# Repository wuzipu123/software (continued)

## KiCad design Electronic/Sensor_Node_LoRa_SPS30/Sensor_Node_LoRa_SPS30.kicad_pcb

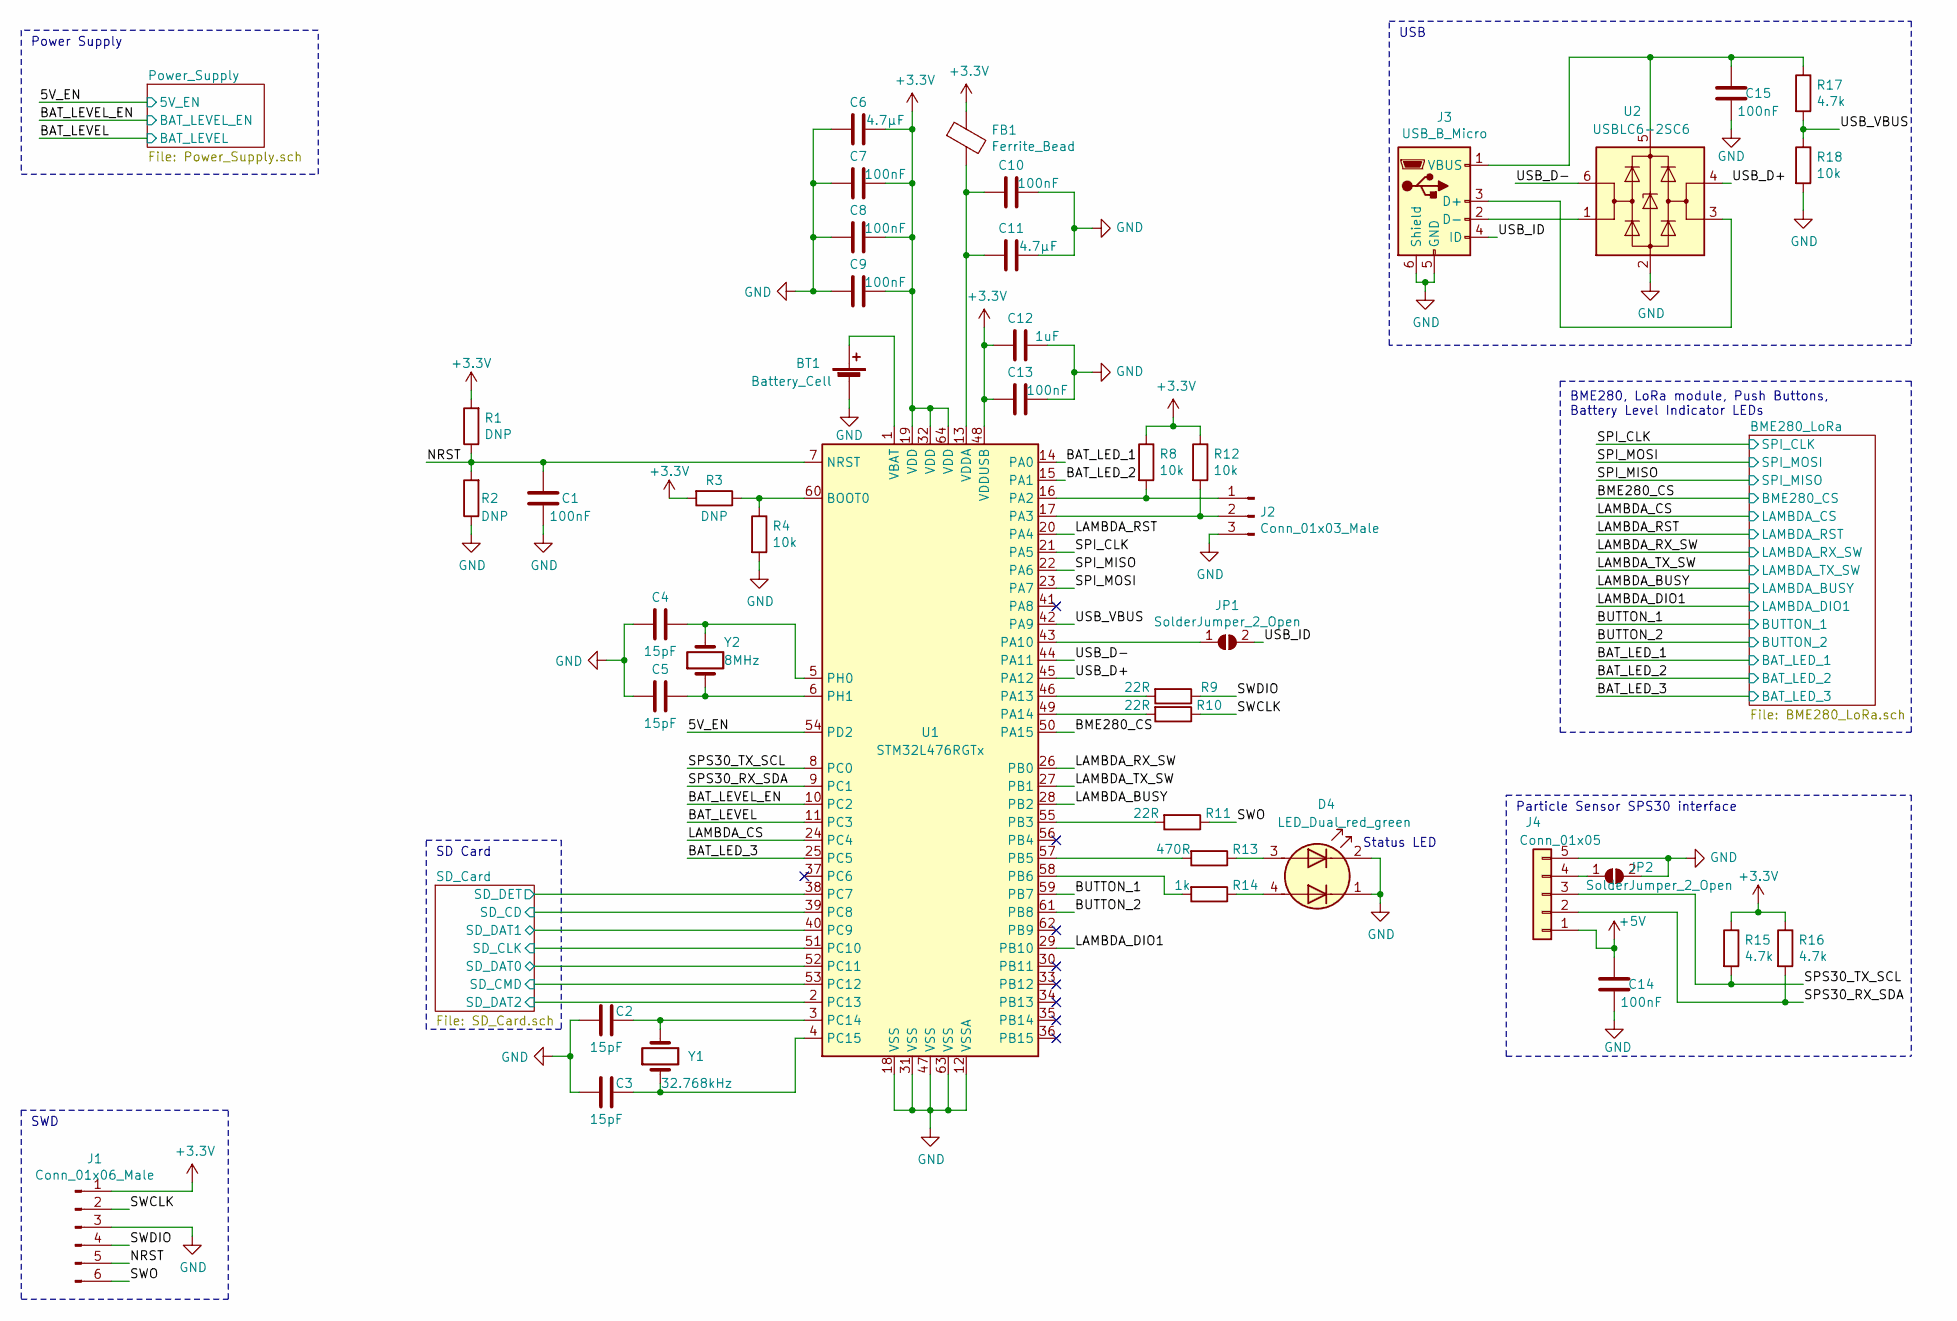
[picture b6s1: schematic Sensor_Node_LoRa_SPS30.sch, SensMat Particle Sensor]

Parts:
BT1: Battery_Cell; BatteryHolder_Keystone_2998_1x6.8mm
C1, C7, C8, C9, C13, C14, C15: 100nF; C_0603_1608Metric_Pad1.05x0.95mm_HandSolder
C2, C3, C4, C5: 15pF; C_0603_1608Metric_Pad1.05x0.95mm_HandSolder
C6, C11: 4.7µF; C_0603_1608Metric_Pad1.05x0.95mm_HandSolder
C10: 100nF; C_0603_1608Metric_Pad1.05x0.95mm_HandSolder; Digi-Key_PN test
C12: 1uF; C_0603_1608Metric_Pad1.05x0.95mm_HandSolder
D4: LED_Dual_red_green; LED_WUERTH_WL-SBCD_0805
FB1: Ferrite_Bead; L_0805_2012Metric_Pad1.15x1.40mm_HandSolder
J1: Conn_01x06_Male; PinHeader_1x06_P2.54mm_Vertical
J2: Conn_01x03_Male; PinHeader_1x03_P2.54mm_Vertical
J3: USB_B_Micro; USB_Micro-B_GCT_USB3076-30-A
J4: Conn_01x05; JST_ZH_B5B-ZH-R_1x05_P1.50mm_Vertical
JP1, JP2: SolderJumper_2_Open; SolderJumper-2_P1.3mm_Open_TrianglePad1.0x1.5mm
R1, R2, R3: DNP; R_0603_1608Metric_Pad1.05x0.95mm_HandSolder
R4, R8, R12, R18: 10k; R_0603_1608Metric_Pad1.05x0.95mm_HandSolder
R9, R10, R11: 22R; R_0603_1608Metric_Pad1.05x0.95mm_HandSolder
R13: 470R; R_0603_1608Metric_Pad1.05x0.95mm_HandSolder
R14: 1k; R_0603_1608Metric_Pad1.05x0.95mm_HandSolder
R15, R16, R17: 4.7k; R_0603_1608Metric_Pad1.05x0.95mm_HandSolder
U1: STM32L476RGTx; LQFP-64_10x10mm_P0.5mm
U2: USBLC6-2SC6; SOT-23-6_Handsoldering
Y1: 32.768kHz; Crystal_SMD_3215-2Pin_3.2x1.5mm_HandSoldering
Y2: 8MHz; Crystal_SMD_5032-2Pin_5.0x3.2mm_HandSoldering

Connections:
+3V3: C6.1, C7.1, C8.1, C9.1, C12.2, C13.2, FB1.1, J1.1, R1.2, R3.2, R8.1, R12.1, R15.1, R16.1, U1.19 (VDD), U1.32 (VDD), U1.48 (VDDUSB), U1.64 (VDD); also elsewhere on the board
+5V: C14.2, J4.1; also elsewhere on the board
/5V_EN: U1.54 (PD2); also elsewhere on the board
/BAT_LED_1: U1.14 (PA0); also elsewhere on the board
/BAT_LED_2: U1.15 (PA1); also elsewhere on the board
/BAT_LED_3: U1.25 (PC5); also elsewhere on the board
/BAT_LEVEL: U1.11 (PC3); also elsewhere on the board
/BAT_LEVEL_EN: U1.10 (PC2); also elsewhere on the board
/BME280_CS: U1.50 (PA15); also elsewhere on the board
/BUTTON_1: U1.59 (PB7); also elsewhere on the board
/BUTTON_2: U1.61 (PB8); also elsewhere on the board
/LAMBDA_BUSY: U1.28 (PB2); also elsewhere on the board
/LAMBDA_CS: U1.24 (PC4); also elsewhere on the board
/LAMBDA_DIO1: U1.29 (PB10); also elsewhere on the board
/LAMBDA_RST: U1.20 (PA4); also elsewhere on the board
/LAMBDA_RX_SW: U1.26 (PB0); also elsewhere on the board
/LAMBDA_TX_SW: U1.27 (PB1); also elsewhere on the board
/NRST: C1.2, J1.5, R1.1, R2.2, U1.7 (NRST)
/SD_Card/SD_CD: U1.39 (PC8); also elsewhere on the board
/SD_Card/SD_CLK: U1.51 (PC10); also elsewhere on the board
/SD_Card/SD_CMD: U1.53 (PC12); also elsewhere on the board
/SD_Card/SD_DAT0: U1.52 (PC11); also elsewhere on the board
/SD_Card/SD_DAT1: U1.40 (PC9); also elsewhere on the board
/SD_Card/SD_DAT2: U1.2 (PC13); also elsewhere on the board
/SD_Card/SD_DET: U1.38 (PC7); also elsewhere on the board
/SPI_CLK: U1.21 (PA5); also elsewhere on the board
/SPI_MISO: U1.22 (PA6); also elsewhere on the board
/SPI_MOSI: U1.23 (PA7); also elsewhere on the board
/SPS30_RX_SDA: J4.2, R16.2, U1.9 (PC1)
/SPS30_TX_SCL: J4.3, R15.2, U1.8 (PC0)
/SWCLK: J1.2, R10.1
/SWDIO: J1.4, R9.1
/SWO: J1.6, R11.1
/USB_D+: U1.45 (PA12), U2.4 (I/O2)
/USB_D-: U1.44 (PA11), U2.6 (I/O1)
/USB_ID: J3.4 (ID), JP1.2 (B)
/USB_VBUS: R17.2, R18.1, U1.42 (PA9)
GND: BT1.2 (-), C1.1, C2.1, C3.1, C4.1, C5.1, C6.2, C7.2, C8.2, C9.2, C10.1, C11.1, C12.1, C13.1, C14.1, C15.1, D4.1 (K2), D4.2 (K1), J1.3, J2.3, J3.5 (GND), J3.6 (Shield), J4.5, JP2.2 (B), R2.1, R4.2, R18.2, U1.12 (VSSA), U1.18 (VSS), U1.31 (VSS), U1.47 (VSS), U1.63 (VSS), U2.2 (GND); also elsewhere on the board
unnamed: BT1.1 (+), U1.1 (VBAT)
unnamed: C2.2, U1.3 (PC14), Y1.2
unnamed: C3.2, U1.4 (PC15), Y1.1
unnamed: C4.2, U1.5 (PH0), Y2.2
unnamed: C5.2, U1.6 (PH1), Y2.1
unnamed: C10.2, C11.2, FB1.2, U1.13 (VDDA)
unnamed: C15.2, J3.1 (VBUS), R17.1, U2.5 (VBUS)
unnamed: D4.3 (A1), R13.1
unnamed: D4.4 (A2), R14.1
unnamed: J2.1, R8.2, U1.16 (PA2)
unnamed: J2.2, R12.2, U1.17 (PA3)
unnamed: J3.2 (D-), U2.1 (I/O1)
unnamed: J3.3 (D+), U2.3 (I/O2)
unnamed: J4.4, JP2.1 (A)
unnamed: JP1.1 (A), U1.43 (PA10)
unnamed: R3.1, R4.1, U1.60 (BOOT0)
unnamed: R9.2, U1.46 (PA13)
unnamed: R10.2, U1.49 (PA14)
unnamed: R11.2, U1.55 (PB3)
unnamed: R13.2, U1.57 (PB5)
unnamed: R14.2, U1.58 (PB6)

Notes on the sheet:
SWD
BME280, LoRa module, Push Buttons, Battery Level Indicator LEDs
SD Card
Particle Sensor SPS30 interface
USB
Power Supply
Status LED

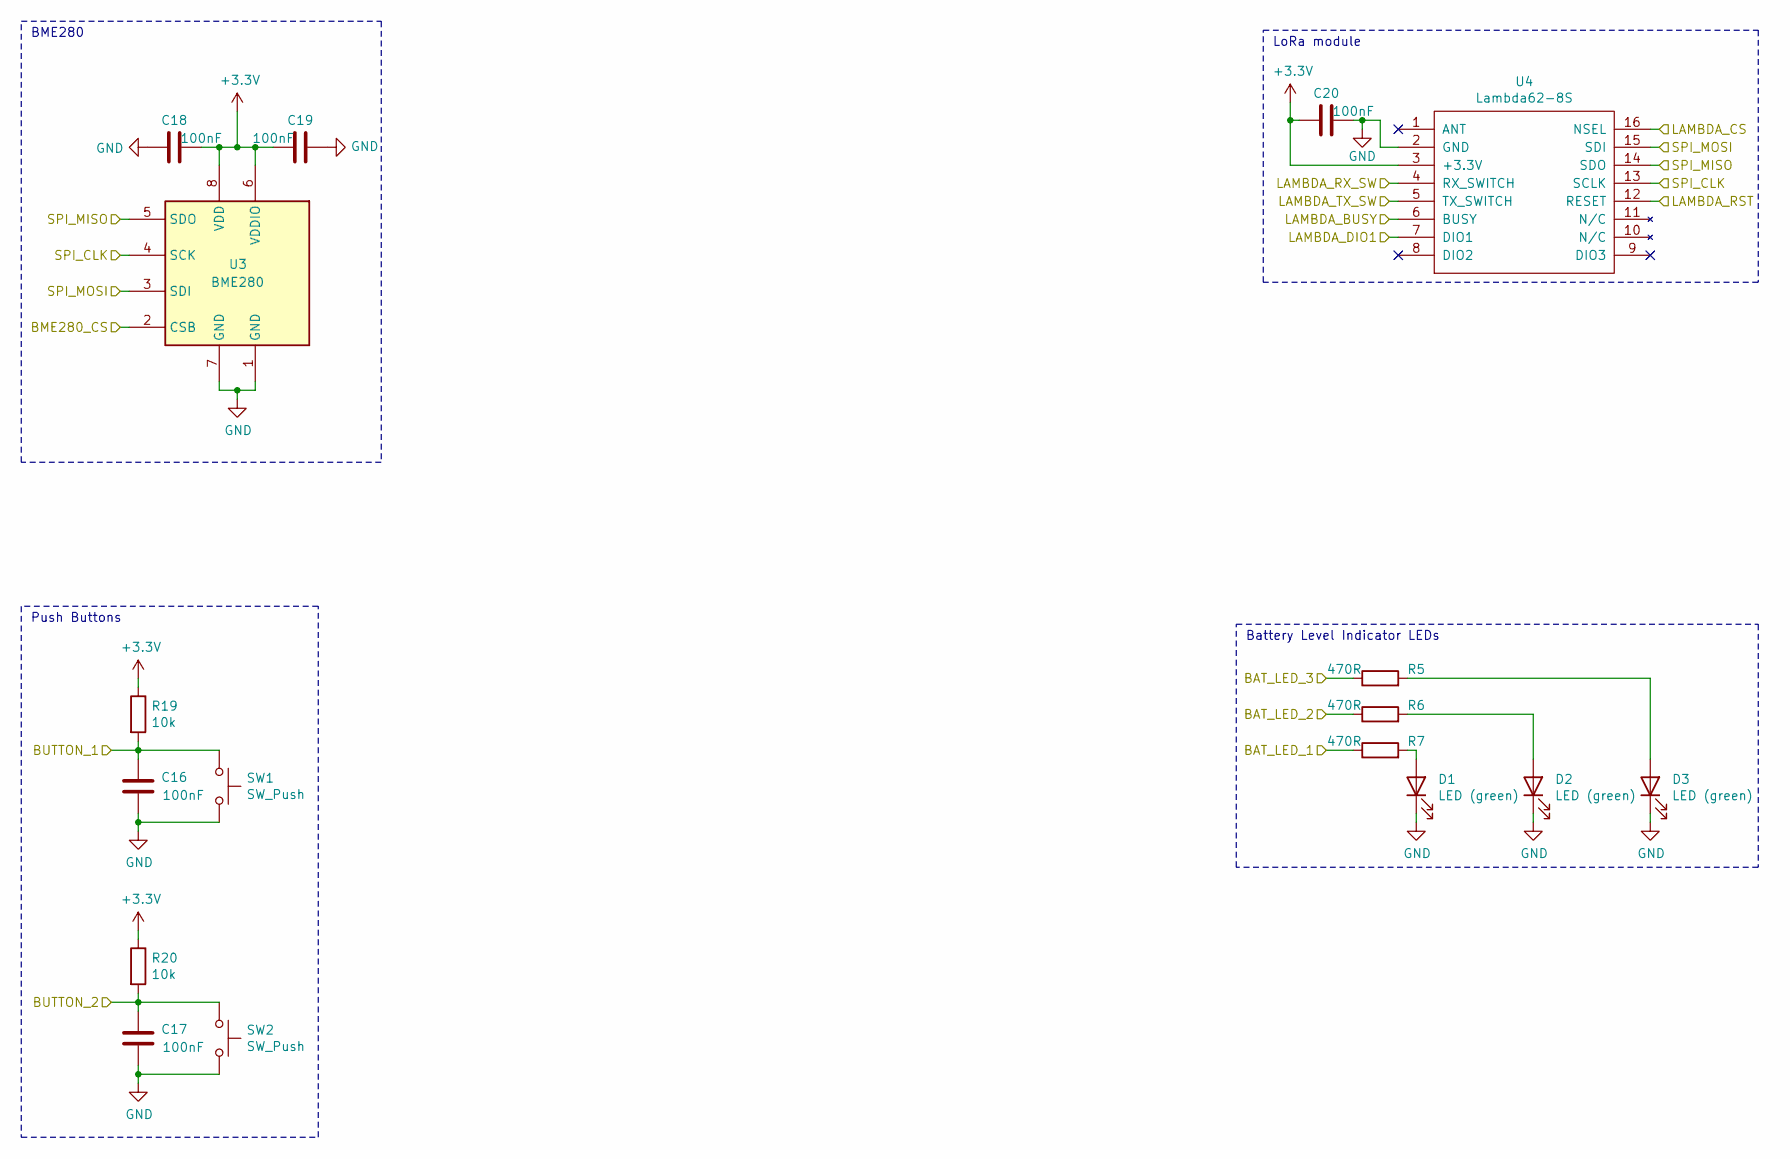
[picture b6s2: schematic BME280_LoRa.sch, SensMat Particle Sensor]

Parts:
C16, C17, C18, C19, C20: 100nF; C_0603_1608Metric_Pad1.05x0.95mm_HandSolder
D1, D2, D3: LED (green); LED_0603_1608Metric_Pad1.05x0.95mm_HandSolder
R5, R6, R7: 470R; R_0603_1608Metric_Pad1.05x0.95mm_HandSolder
R19, R20: 10k; R_0603_1608Metric_Pad1.05x0.95mm_HandSolder
SW1, SW2: SW_Push; SW_Tactile_SPST_Angled_PTS645Vx58-2LFS
U3: BME280; Bosch_LGA-8_2.5x2.5mm_P0.65mm_ClockwisePinNumbering
U4: Lambda62-8S

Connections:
+3V3: C18.1, C19.2, C20.2, R19.1, R20.1, U3.6 (VDDIO), U3.8 (VDD), U4.3 (+3.3V); also elsewhere on the board
/BAT_LED_1: R7.1; also elsewhere on the board
/BAT_LED_2: R6.1; also elsewhere on the board
/BAT_LED_3: R5.1; also elsewhere on the board
/BME280_CS: U3.2 (CSB); also elsewhere on the board
/BUTTON_1: C16.2, R19.2, SW1.1; also elsewhere on the board
/BUTTON_2: C17.2, R20.2, SW2.1; also elsewhere on the board
/LAMBDA_BUSY: U4.6 (BUSY); also elsewhere on the board
/LAMBDA_CS: U4.16 (NSEL); also elsewhere on the board
/LAMBDA_DIO1: U4.7 (DIO1); also elsewhere on the board
/LAMBDA_RST: U4.12 (RESET); also elsewhere on the board
/LAMBDA_RX_SW: U4.4 (RX_SWITCH); also elsewhere on the board
/LAMBDA_TX_SW: U4.5 (TX_SWITCH); also elsewhere on the board
/SPI_CLK: U3.4 (SCK), U4.13 (SCLK); also elsewhere on the board
/SPI_MISO: U3.5 (SDO), U4.14 (SDO); also elsewhere on the board
/SPI_MOSI: U3.3 (SDI), U4.15 (SDI); also elsewhere on the board
GND: C16.1, C17.1, C18.2, C19.1, C20.1, D1.1 (K), D2.1 (K), D3.1 (K), SW1.2, SW2.2, U3.1 (GND), U3.7 (GND), U4.2 (GND); also elsewhere on the board
unnamed: D1.2 (A), R7.2
unnamed: D2.2 (A), R6.2
unnamed: D3.2 (A), R5.2

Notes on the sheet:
LoRa module
BME280
Push Buttons
Battery Level Indicator LEDs

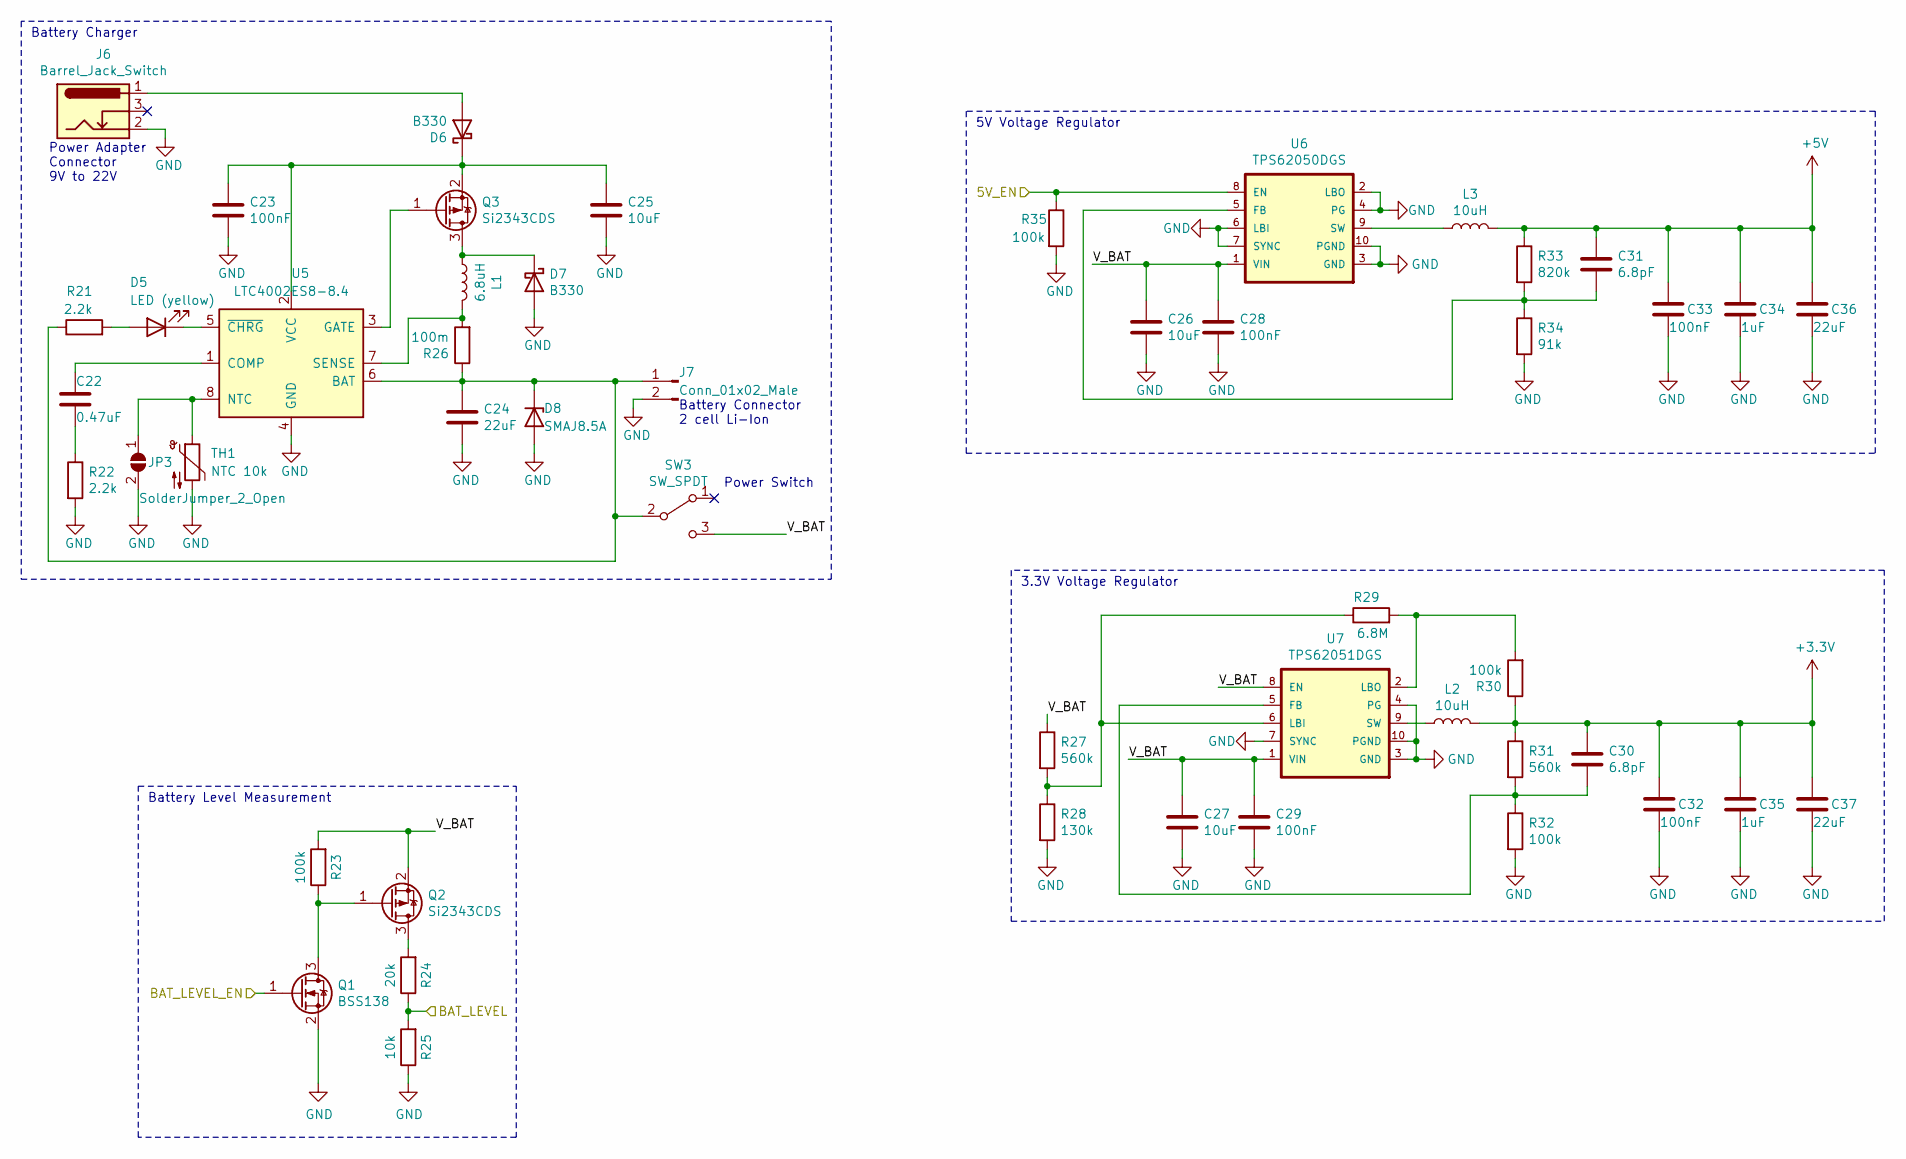
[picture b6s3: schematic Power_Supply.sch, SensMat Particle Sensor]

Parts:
C22: 0.47uF; C_0603_1608Metric_Pad1.05x0.95mm_HandSolder
C23, C28, C29, C32, C33: 100nF; C_0603_1608Metric_Pad1.05x0.95mm_HandSolder
C24, C36, C37: 22uF; C_0603_1608Metric_Pad1.05x0.95mm_HandSolder
C25, C26, C27: 10uF; C_0603_1608Metric_Pad1.05x0.95mm_HandSolder
C30, C31: 6.8pF; C_0603_1608Metric_Pad1.05x0.95mm_HandSolder
C34, C35: 1uF; C_0603_1608Metric_Pad1.05x0.95mm_HandSolder
D5: LED (yellow); LED_0603_1608Metric_Pad1.05x0.95mm_HandSolder
D6, D7: B330; D_SMB-SMC_Universal_Handsoldering
D8: SMAJ8.5A; D_SMA
J6: Barrel_Jack_Switch; BarrelJack_CUI_PJ-051A_Horizontal
J7: Conn_01x02_Male; PinSocket_1x02_P2.54mm_Vertical
JP3: SolderJumper_2_Open; SolderJumper-2_P1.3mm_Open_TrianglePad1.0x1.5mm
L1: 6.8uH; L_Wuerth_LQS-6045
L2, L3: 10uH; L_Wuerth_LQS-5040
Q1: BSS138; SOT-23
Q2, Q3: Si2343CDS; SOT-23
R21, R22: 2.2k; R_0603_1608Metric_Pad1.05x0.95mm_HandSolder
R23, R30, R32, R35: 100k; R_0603_1608Metric_Pad1.05x0.95mm_HandSolder
R24: 20k; R_0603_1608Metric_Pad1.05x0.95mm_HandSolder
R25: 10k; R_0603_1608Metric_Pad1.05x0.95mm_HandSolder
R26: 100m; R_1206_3216Metric_Pad1.42x1.75mm_HandSolder
R27, R31: 560k; R_0603_1608Metric_Pad1.05x0.95mm_HandSolder
R28: 130k; R_0603_1608Metric_Pad1.05x0.95mm_HandSolder
R29: 6.8M; R_0603_1608Metric_Pad1.05x0.95mm_HandSolder
R33: 820k; R_0603_1608Metric_Pad1.05x0.95mm_HandSolder
R34: 91k; R_0603_1608Metric_Pad1.05x0.95mm_HandSolder
SW3: SW_SPDT; SW_CK_SK-12F17-G_7_SPDT_Angled
TH1: NTC 10k; R_1206_3216Metric_Pad1.42x1.75mm_HandSolder
U5: LTC4002ES8-8.4; SOIC-8_3.9x4.9mm_P1.27mm
U6: TPS62050DGS; MSOP-10_3x3mm_P0.5mm
U7: TPS62051DGS; MSOP-10_3x3mm_P0.5mm

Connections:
+3V3: C30.1, C32.1, C35.1, C37.1, L2.2, R30.1, R31.1; also elsewhere on the board
+5V: C31.1, C33.1, C34.1, C36.1, L3.2, R33.1; also elsewhere on the board
/5V_EN: R35.1, U6.8 (EN); also elsewhere on the board
/BAT_LEVEL: R24.1, R25.2; also elsewhere on the board
/BAT_LEVEL_EN: Q1.1 (G); also elsewhere on the board
/Power_Supply/V_BAT: C26.1, C27.1, C28.1, C29.1, Q2.2 (S), R23.2, R27.1, SW3.3 (C), U6.1 (VIN), U7.1 (VIN), U7.8 (EN)
GND: C23.2, C24.2, C25.2, C26.2, C27.2, C28.2, C29.2, C32.2, C33.2, C34.2, C35.2, C36.2, C37.2, D7.2 (A), D8.2 (A2), J6.2, J7.2, JP3.2 (B), Q1.2 (S), R22.2, R25.1, R28.2, R32.2, R34.2, R35.2, TH1.2, U5.4 (GND), U6.2 (LBO), U6.3 (GND), U6.4 (PG), U6.6 (LBI), U6.7 (SYNC), U6.10 (PGND), U7.3 (GND), U7.4 (PG), U7.7 (SYNC), U7.10 (PGND); also elsewhere on the board
unnamed: C22.1, U5.1 (COMP)
unnamed: C22.2, R22.1
unnamed: C23.1, C25.1, D6.1 (K), Q3.2 (S), U5.2 (VCC)
unnamed: C24.1, D8.1 (A1), J7.1, R21.1, R26.1, SW3.2 (B), U5.6 (BAT)
unnamed: C30.2, R31.2, R32.1, U7.5 (FB)
unnamed: C31.2, R33.2, R34.1, U6.5 (FB)
unnamed: D5.1 (K), U5.5 (~CHRG~)
unnamed: D5.2 (A), R21.2
unnamed: D6.2 (A), J6.1
unnamed: D7.1 (K), L1.1, Q3.3 (D)
unnamed: JP3.1 (A), TH1.1, U5.8 (NTC)
unnamed: L1.2, R26.2, U5.7 (SENSE)
unnamed: L2.1, U7.9 (SW)
unnamed: L3.1, U6.9 (SW)
unnamed: Q1.3 (D), Q2.1 (G), R23.1
unnamed: Q2.3 (D), R24.2
unnamed: Q3.1 (G), U5.3 (GATE)
unnamed: R27.2, R28.1, R29.1, U7.6 (LBI)
unnamed: R29.2, R30.2, U7.2 (LBO)

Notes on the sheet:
Battery Connector 2 cell Li-Ion
Power Switch
Power Adapter Connector 9V to 22V
5V Voltage Regulator
3.3V Voltage Regulator
Battery Level Measurement
Battery Charger

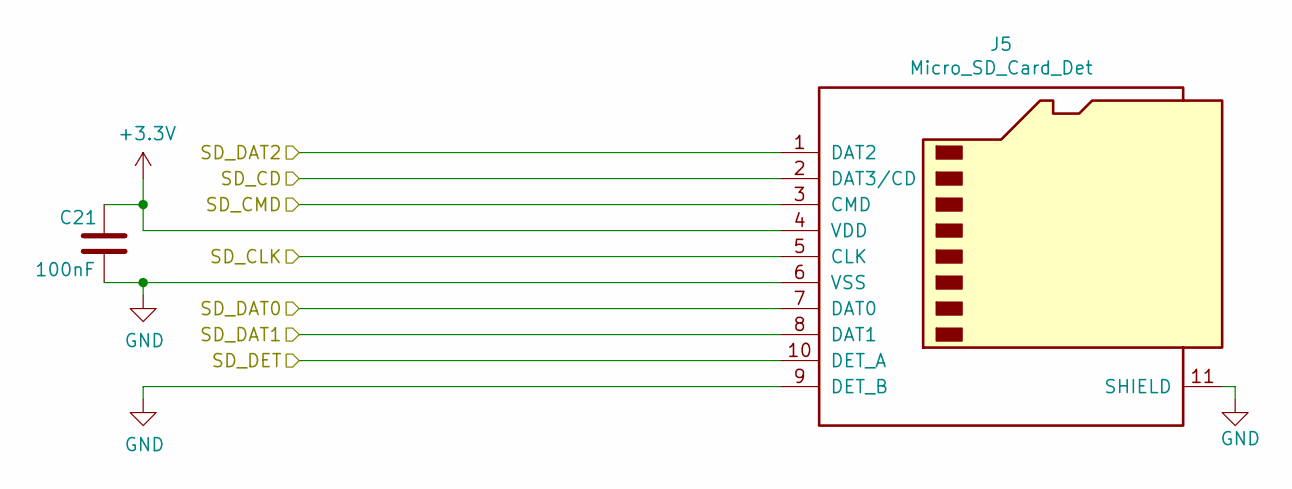
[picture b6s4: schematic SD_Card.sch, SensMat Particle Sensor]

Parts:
C21: 100nF; C_0603_1608Metric_Pad1.05x0.95mm_HandSolder
J5: Micro_SD_Card_Det; microSD_HC_Hirose_DM3AT-SF-PEJM5

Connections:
+3V3: C21.1, J5.4 (VDD); also elsewhere on the board
/SD_Card/SD_CD: J5.2 (DAT3/CD); also elsewhere on the board
/SD_Card/SD_CLK: J5.5 (CLK); also elsewhere on the board
/SD_Card/SD_CMD: J5.3 (CMD); also elsewhere on the board
/SD_Card/SD_DAT0: J5.7 (DAT0); also elsewhere on the board
/SD_Card/SD_DAT1: J5.8 (DAT1); also elsewhere on the board
/SD_Card/SD_DAT2: J5.1 (DAT2); also elsewhere on the board
/SD_Card/SD_DET: J5.10 (DET_A); also elsewhere on the board
GND: C21.2, J5.6 (VSS), J5.9 (DET_B), J5.11 (SHIELD); also elsewhere on the board

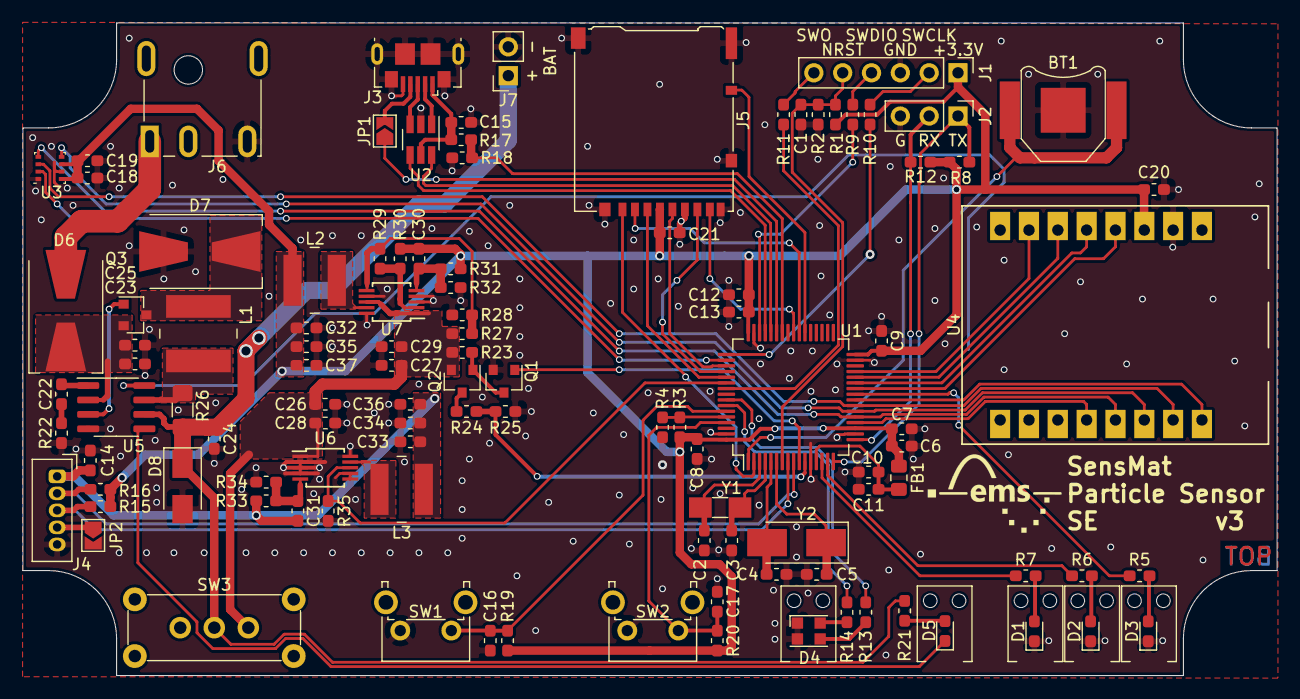
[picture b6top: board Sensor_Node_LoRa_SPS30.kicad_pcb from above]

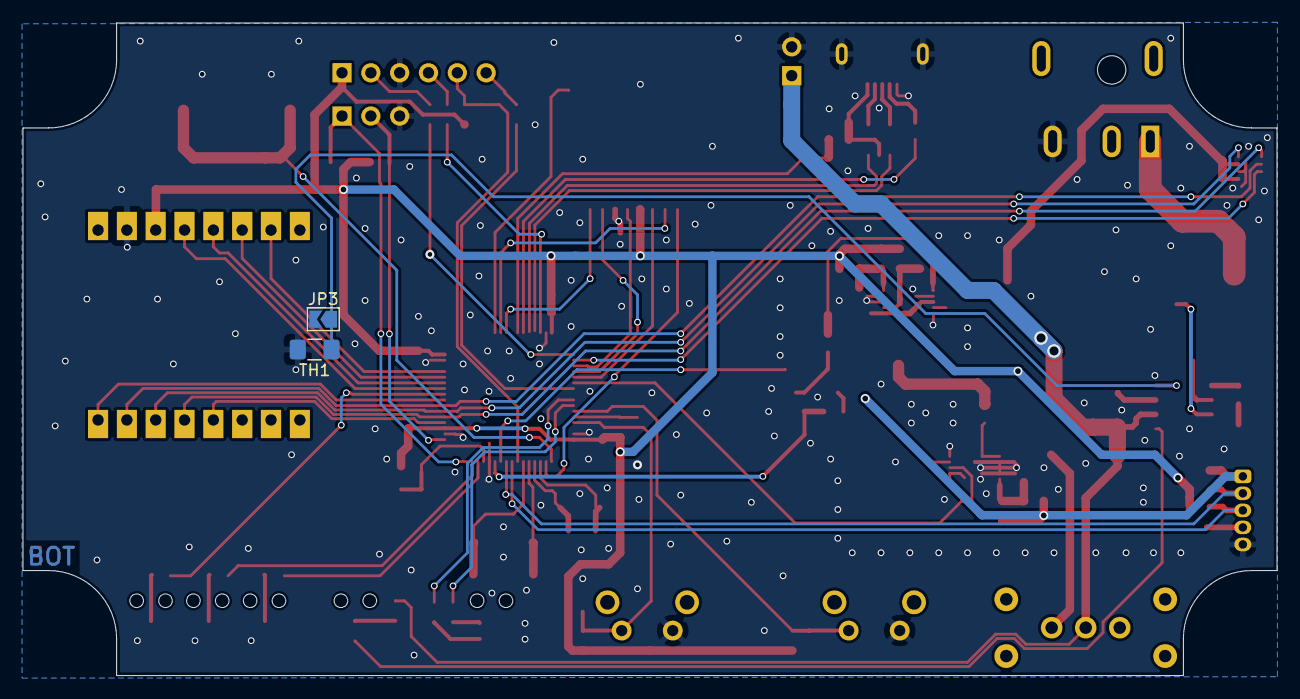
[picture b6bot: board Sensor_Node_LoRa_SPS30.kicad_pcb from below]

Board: 2 copper layers, 110.5 x 57.5 mm, 111 parts (2 on the bottom side), 82 nets.

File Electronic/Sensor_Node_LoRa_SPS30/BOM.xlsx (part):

Source: | SensMat/Electronic/Sensor_Node_LoRa_SPS30/Sensor_Node_LoRa_SPS30.sch
Date: | Do 10 May 2021 10:51:11
Tool: | Eeschema 5.1.8
Generator: | /usr/share/kicad/plugins/bom_csv_grouped_by_value_with_fp.py
Component Count: | 111
Ref | Qnty | Order | Value | Cmp name | Footprint | Description | Digikey Nr. | Digikey-Link
BT1, | 1 |  | Battery_Cell | Battery_Cell | Battery:BatteryHolder_Keystone_2998_1x6.8mm | Single-cell battery holder | 36-2998-ND | https://www.digikey.at/products/de?keywords=36-2998-ND
C1, C7, C8, C9, C10, C13, C14, C15, C16, C17, C18, C19, C20, C21, C23, C28, C29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 | 19 |  | 100nF | C | Capacitor_SMD:C_0603_1608Metric_Pad1.05x0.95mm_HandSolder | Unpolarized capacitor | 1276-1857-1-ND | https://www.digikey.at/products/de?keywords=1276-1857-1-ND
C2, C3, C4, C5, | 4 |  | 15pF | C | Capacitor_SMD:C_0603_1608Metric_Pad1.05x0.95mm_HandSolder | Unpolarized capacitor | 1276-1296-1-ND | https://www.digikey.at/products/de?keywords=1276-1296-1-ND
C6, C11, | 2 |  | 4.7µF | C | Capacitor_SMD:C_0603_1608Metric_Pad1.05x0.95mm_HandSolder | Unpolarized capacitor | 1276-1907-1-ND | https://www.digikey.at/products/de?keywords=1276-1907-1-ND
C12, C34, C35, | 3 |  | 1uF | C | Capacitor_SMD:C_0603_1608Metric_Pad1.05x0.95mm_HandSolder | Unpolarized capacitor | 1276-1182-1-ND | https://www.digikey.at/products/de?keywords=1276-1182-1-ND
C22, | 1 |  | 0.47uF | C | Capacitor_SMD:C_0603_1608Metric_Pad1.05x0.95mm_HandSolder | Unpolarized capacitor | 1276-1895-1-ND | https://www.digikey.at/products/de?keywords=1276-1895-1-ND
C24, C36, C37, | 3 |  | 22uF | C | Capacitor_SMD:C_0603_1608Metric_Pad1.05x0.95mm_HandSolder | Unpolarized capacitor | 445-9077-1-ND | https://www.digikey.at/products/de?keywords=445-9077-1-ND
C25, C26, C27, | 3 |  | 10uF | C | Capacitor_SMD:C_0603_1608Metric_Pad1.05x0.95mm_HandSolder | Unpolarized capacitor | 587-6023-1-ND | https://www.digikey.at/products/de?keywords=587-6023-1-ND
C30, C31, | 2 |  | 6.8pF | C | Capacitor_SMD:C_0603_1608Metric_Pad1.05x0.95mm_HandSolder | Unpolarized capacitor | 1276-1793-1-ND | https://www.digikey.at/products/de?keywords=1276-1793-1-ND
D1, D2, D3, | 3 |  | LED (green) | LED | LED_SMD:LED_0603_1608Metric_Pad1.05x0.95mm_HandSolder | Light emitting diode green | 732-4980-1-ND | https://www.digikey.at/products/de?keywords=732-4980-1-ND
D4, | 1 |  | LED_Dual_red_green | LED_Dual_CCAA | LED_SMD:LED_WUERTH_WL-SBCD_0805 | Dual LED, cathodes on pins 1 and 2 | 732-150080RV54050CT-ND | https://www.digikey.at/products/de?keywords=732-150080RV54050CT-ND
D5, | 1 |  | LED (yellow) | LED | LED_SMD:LED_0603_1608Metric_Pad1.05x0.95mm_HandSolder | Light emitting diode yellow | 732-4981-6-ND | https://www.digikey.at/products/de?keywords=732-4981-6-ND
D6, D7, | 2 |  | B330 | B330 | Diode_SMD:D_SMB-SMC_Universal_Handsoldering | 30V 3A Schottky Barrier Rectifier Diode, SMC | B330-FDICT-ND | https://www.digikey.at/products/de?keywords=B330-FDICT-ND
D8, | 1 |  | SMAJ8.5A | 5KPxxA | Diode_SMD:D_SMA | 5000W unidirectional Transient Voltage Suppressor, P-600 | SMAJ8.5A-FDICT-ND | https://www.digikey.at/products/de?keywords=SMAJ8.5A-FDICT-ND
FB1, | 1 |  | Ferrite_Bead | Ferrite_Bead | Inductor_SMD:L_0805_2012Metric_Pad1.15x1.40mm_HandSolder | Ferrite bead | 541-4362-1-ND | https://www.digikey.at/products/de?keywords=541-4362-1-ND
J1, | 1 |  | Conn_01x06_Male | Conn_01x06_Male | Connector_PinHeader_2.54mm:PinHeader_1x06_P2.54mm_Vertical | Generic connector, single row, 01x06, |  | https://www.digikey.at/products/de?keywords=
J2, | 1 |  | Conn_01x03_Male | Conn_01x03_Male | Connector_PinHeader_2.54mm:PinHeader_1x03_P2.54mm_Vertical | Generic connector, single row, 01x03, |  | https://www.digikey.at/products/de?keywords=
J3, | 1 |  | USB_B_Micro | USB_B_Micro | Connector_USB:USB_Micro-B_GCT_USB3076-30-A | USB Micro Type B connector | 2073-USB3076-30-ACT-ND | https://www.digikey.at/products/de?keywords=2073-USB3076-30-ACT-ND
J4, | 1 |  | Conn_01x05 | Conn_01x05 | Connector_JST:JST_ZH_B5B-ZH-R_1x05_P1.50mm_Vertical | Generic connector, single row, 01x05, | 455-1660-ND | https://www.digikey.at/products/de?keywords=455-1660-ND
J5, | 1 |  | Micro_SD_Card_Det | Micro_SD_Card_Det | Connector_Card:microSD_HC_Hirose_DM3AT-SF-PEJM5 | Micro SD Card Socket with card detection pins | HR1964CT-ND | https://www.digikey.at/products/de?keywords=HR1964CT-ND
J6, | 1 |  | Barrel_Jack_Switch | Barrel_Jack_Switch | Connector_BarrelJack:BarrelJack_CUI_PJ-051A_Horizontal | DC Barrel Jack with an internal switch | CP-051A-ND | https://www.digikey.at/products/de?keywords=CP-051A-ND
J7, | 1 |  | Conn_01x02_Male | Conn_01x02_Male | Connector_PinSocket_2.54mm:PinSocket_1x02_P2.54mm_Vertical | Generic connector, single row, 01x02, | 900-0022053021-ND | https://www.digikey.at/products/de?keywords=900-0022053021-ND
JP1, JP2, JP3, | 3 |  | SolderJumper_2_Open | SolderJumper_2_Open | Jumper:SolderJumper-2_P1.3mm_Open_TrianglePad1.0x1.5mm | Solder Jumper, 2-pole, open |  | https://www.digikey.at/products/de?keywords=
L1, | 1 |  | 6.8uH | L | Inductor_SMD:L_Wuerth_LQS-6045 | Inductor | 732-5547-1-ND | https://www.digikey.at/products/de?keywords=732-5547-1-ND
L2, L3, | 2 |  | 10uH | L | Inductor_SMD:L_Wuerth_LQS-5040 | Inductor | 732-5519-1-ND | https://www.digikey.at/products/de?keywords=732-5519-1-ND
Q1, | 1 |  | BSS138 | BSS138 | Package_TO_SOT_SMD:SOT-23 | 50V Vds, 0.22A Id, N-Channel MOSFET, SOT-23 | BSS138CT-ND | https://www.digikey.at/products/de?keywords=BSS138CT-ND
Q2, Q3, | 2 |  | Si2343CDS | Si2343CDS | Package_TO_SOT_SMD:SOT-23 | -3.6A Id, -30V Vds, P-Channel MOSFET, SOT-23 | SI2343CDS-T1-GE3CT-ND | https://www.digikey.at/products/de?keywords=SI2343CDS-T1-GE3CT-ND
R1, R2, R3, | 3 |  | DNP | R | Resistor_SMD:R_0603_1608Metric_Pad1.05x0.95mm_HandSolder | Resistor |  | https://www.digikey.at/products/de?keywords=
R4, R8, R12, R18, R19, R20, R25, | 7 |  | 10k | R | Resistor_SMD:R_0603_1608Metric_Pad1.05x0.95mm_HandSolder | Resistor | 311-10.0KHRCT-ND | https://www.digikey.at/products/de?keywords=311-10.0KHRCT-ND
R5, R6, R7, R13, | 4 |  | 470R | R | Resistor_SMD:R_0603_1608Metric_Pad1.05x0.95mm_HandSolder | Resistor | 311-470HRCT-ND | https://www.digikey.at/products/de?keywords=311-470HRCT-ND
R9, R10, R11, | 3 |  | 22R | R | Resistor_SMD:R_0603_1608Metric_Pad1.05x0.95mm_HandSolder | Resistor | 311-22.0HRCT-ND | https://www.digikey.at/products/de?keywords=311-22.0HRCT-ND
R14, | 1 |  | 1k | R | Resistor_SMD:R_0603_1608Metric_Pad1.05x0.95mm_HandSolder | Resistor | 311-1.00KHRCT-ND | https://www.digikey.at/products/de?keywords=311-1.00KHRCT-ND
R15, R16, R17, | 3 |  | 4.7k | R | Resistor_SMD:R_0603_1608Metric_Pad1.05x0.95mm_HandSolder | Resistor | YAG3613CT-ND | https://www.digikey.at/products/de?keywords=YAG3613CT-ND
R21, R22, | 2 |  | 2.2k | R | Resistor_SMD:R_0603_1608Metric_Pad1.05x0.95mm_HandSolder | Resistor | 311-2.20KHRCT-ND | https://www.digikey.at/products/de?keywords=311-2.20KHRCT-ND
R23, R30, R32, R35, | 4 |  | 100k | R | Resistor_SMD:R_0603_1608Metric_Pad1.05x0.95mm_HandSolder | Resistor | 311-100KHRCT-ND | https://www.digikey.at/products/de?keywords=311-100KHRCT-ND
R24, | 1 |  | 20k | R | Resistor_SMD:R_0603_1608Metric_Pad1.05x0.95mm_HandSolder | Resistor | 311-20.0KHRCT-ND | https://www.digikey.at/products/de?keywords=311-20.0KHRCT-ND
R26, | 1 |  | 100m | R | Resistor_SMD:R_1206_3216Metric_Pad1.42x1.75mm_HandSolder | Resistor 1W, RS: ERJ8BWFR100V | P.10AUCT-ND | https://www.digikey.at/products/de?keywords=P.10AUCT-ND
R27, | 1 |  | 560k | R | Resistor_SMD:R_0603_1608Metric_Pad1.05x0.95mm_HandSolder | Resistor | 311-560KHRCT-ND | https://www.digikey.at/products/de?keywords=311-560KHRCT-ND
R28, | 1 |  | 130k | R | Resistor_SMD:R_0603_1608Metric_Pad1.05x0.95mm_HandSolder | Resistor | 311-130KHRCT-ND | https://www.digikey.at/products/de?keywords=311-130KHRCT-ND
R29, | 1 |  | 6.8M | R | Resistor_SMD:R_0603_1608Metric_Pad1.05x0.95mm_HandSolder | Resistor | 541-6.80MHCT-ND | https://www.digikey.at/products/de?keywords=541-6.80MHCT-ND
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
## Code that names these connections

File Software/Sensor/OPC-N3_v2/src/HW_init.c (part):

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	 __HAL_RCC_GPIOB_CLK_ENABLE();
	 GPIO_InitTypeDef  GPIO_InitStruct;

	 //PA1 output - active low led for testing only
	GPIO_InitStruct.Pin = (GPIO_PIN_1);
	GPIO_InitStruct.Mode = GPIO_MODE_OUTPUT_PP;
	GPIO_InitStruct.Pull = GPIO_PULLUP;
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	HAL_GPIO_WritePin(GPIOA, GPIO_PIN_1, GPIO_PIN_RESET);

	// read card adress via hardware, reset pins for low power consumption
	//PA8 input - add0 - card address bit0
	GPIO_InitStruct.Pin = (GPIO_PIN_8);
	GPIO_InitStruct.Mode = GPIO_MODE_INPUT;
	GPIO_InitStruct.Pull = GPIO_PULLUP;
	HAL_GPIO_Init(GPIOA, &GPIO_InitStruct);
	*card_address = HAL_GPIO_ReadPin(GPIOA, GPIO_PIN_8);

	//PA9 input - add1 - card address bit1
	GPIO_InitStruct.Pin = (GPIO_PIN_9);
	GPIO_InitStruct.Mode = GPIO_MODE_INPUT;
	GPIO_InitStruct.Pull = GPIO_PULLUP;
	HAL_GPIO_Init(GPIOA, &GPIO_InitStruct);
	*card_address |= ((HAL_GPIO_ReadPin(GPIOA, GPIO_PIN_9))<<1);

	//PA10 input - add2 - card address bit2
	GPIO_InitStruct.Pin = (GPIO_PIN_10);
	GPIO_InitStruct.Mode = GPIO_MODE_INPUT;
	GPIO_InitStruct.Pull = GPIO_PULLUP;
	HAL_GPIO_Init(GPIOA, &GPIO_InitStruct);
	*card_address |= ((HAL_GPIO_ReadPin(GPIOA, GPIO_PIN_10))<<2);

	//PA8 input - add0 - card address bit0 set to low power
	GPIO_InitStruct.Pin = (GPIO_PIN_8);
	GPIO_InitStruct.Mode = GPIO_MODE_ANALOG;
	GPIO_InitStruct.Pull = GPIO_NOPULL;
	HAL_GPIO_Init(GPIOA, &GPIO_InitStruct);

	//PA9 input - add1 - card address bit1 set to low power
	GPIO_InitStruct.Pin = (GPIO_PIN_9);
	GPIO_InitStruct.Mode = GPIO_MODE_ANALOG;
	GPIO_InitStruct.Pull = GPIO_NOPULL;
	HAL_GPIO_Init(GPIOA, &GPIO_InitStruct);

	//PA10 input - add2 - card address bit2 set to low power
	GPIO_InitStruct.Pin = (GPIO_PIN_10);
	GPIO_InitStruct.Mode = GPIO_MODE_ANALOG;
	GPIO_InitStruct.Pull = GPIO_NOPULL;
	HAL_GPIO_Init(GPIOA, &GPIO_InitStruct);

	/*use controll pins if necessary, otherwise leave unconfigured
	//PA11 input - cp0 - control bit0
	GPIO_InitStruct.Pin = (GPIO_PIN_11);
	GPIO_InitStruct.Mode = GPIO_MODE_INPUT;
	GPIO_InitStruct.Pull = GPIO_PULLUP;
	HAL_GPIO_Init(GPIOA, &GPIO_InitStruct);

	//PA12 input - cp1 - control bit1
	GPIO_InitStruct.Pin = (GPIO_PIN_12);
	GPIO_InitStruct.Mode = GPIO_MODE_INPUT;
	GPIO_InitStruct.Pull = GPIO_PULLUP;
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void HW_init_UART(UART_HandleTypeDef *UartHandle)
{

	/* PA3 UART1_RX only used for full duplex communication
	 * PA4 UART1_TX
	 * PC14 UART1_RE
	 * PC15 UART1_DE
	 */
	GPIO_InitTypeDef GPIO_Init_UART;

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	HAL_GPIO_Init(GPIOC, &GPIO_Init_UART);
	HAL_GPIO_WritePin(GPIOC, GPIO_PIN_15, GPIO_PIN_RESET);

	//PA3 configured as RX
	GPIO_Init_UART.Pin = GPIO_PIN_3;
	GPIO_Init_UART.Mode=GPIO_MODE_AF_PP;
	GPIO_Init_UART.Pull=GPIO_PULLUP;
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	GPIO_Init_UART.Alternate = GPIO_AF4_USART2;
	HAL_GPIO_Init(GPIOA, &GPIO_Init_UART);

	//PA2 configured as TX
	GPIO_Init_UART.Pin 			= GPIO_PIN_2;
	GPIO_Init_UART.Mode      	= GPIO_MODE_AF_PP;
	GPIO_Init_UART.Pull			= GPIO_PULLUP;
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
